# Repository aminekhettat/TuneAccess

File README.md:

# TuneAccess
Music instrument tuner adapted for people with visual disability

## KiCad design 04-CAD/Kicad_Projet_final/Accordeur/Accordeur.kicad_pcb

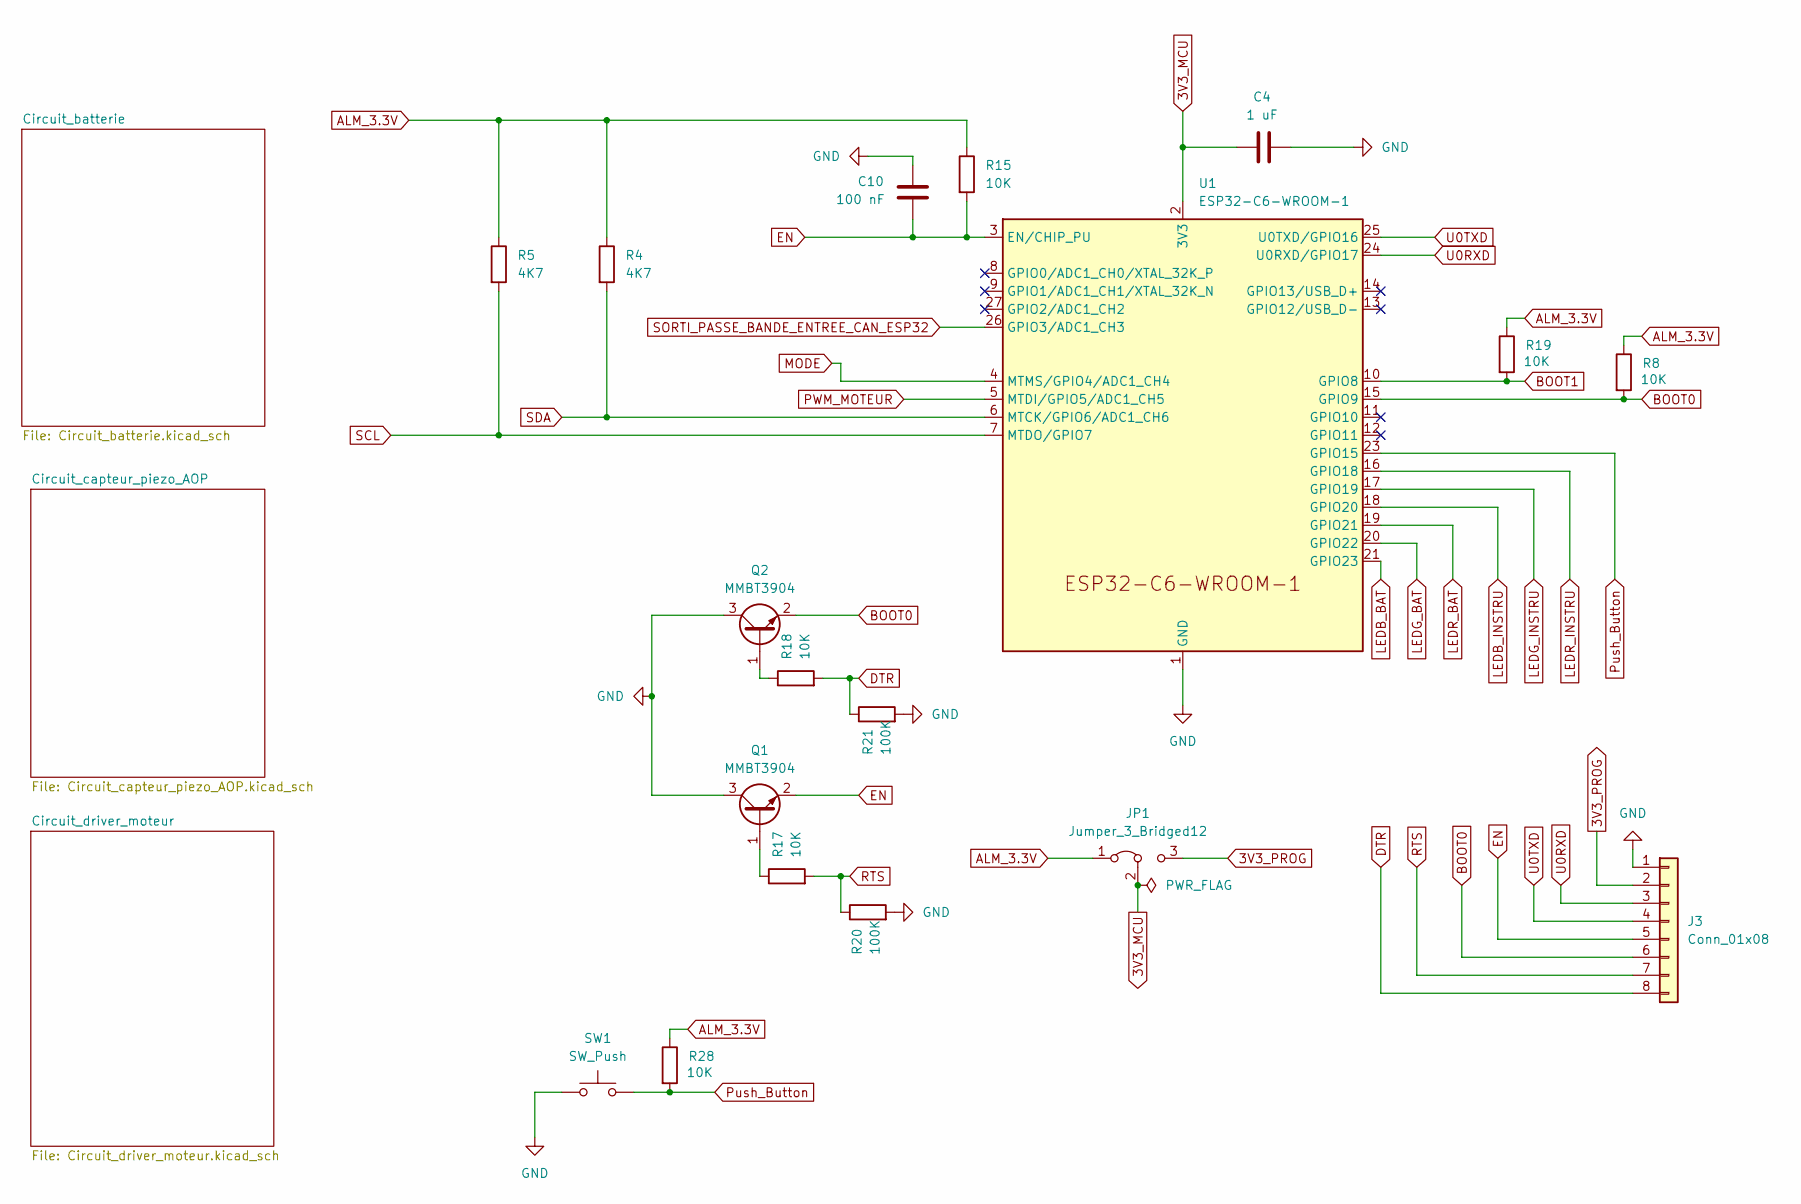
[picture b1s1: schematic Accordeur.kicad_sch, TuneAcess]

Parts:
C4: 1 uF; C_0805_2012Metric
C10: 100 nF; C_0805_2012Metric
J3: Conn_01x08; PinHeader_1x08_P2.54mm_Horizontal
JP1: Jumper_3_Bridged12; PinHeader_1x03_P2.54mm_Vertical
Q1, Q2: MMBT3904; SOT-23
R4, R5: 4K7; R_0402_1005Metric
R8, R15, R17, R18, R19, R28: 10K; R_0402_1005Metric
R20, R21: 100K; R_0402_1005Metric
SW1: SW_Push; SW_PUSH_6mm_H13mm
U1: ESP32-C6-WROOM-1

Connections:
3V3_MCU: C4.2, JP1.2 (C), U1.2 (3V3)
3V3_PROG: J3.2, JP1.3 (B)
ALM_3.3V: JP1.1 (A), R4.1, R5.1, R8.1, R15.1, R19.1, R28.1; also elsewhere on the board
BOOT0: J3.6, Q2.2 (E), R8.2, U1.15 (GPIO9)
BOOT1: R19.2, U1.10 (GPIO8)
DTR: J3.8, R18.2, R21.1
EN: C10.2, J3.5, Q1.2 (E), R15.2, U1.3 (EN/CHIP_PU)
GND: C4.1, C10.1, J3.1, Q1.3 (C), Q2.3 (C), R20.2, R21.2, SW1.1, U1.1 (GND), U1.28 (GND), U1.29 (GND); also elsewhere on the board
LEDB_BAT: U1.21 (GPIO23); also elsewhere on the board
LEDB_INSTRU: U1.18 (GPIO20); also elsewhere on the board
LEDG_BAT: U1.20 (GPIO22); also elsewhere on the board
LEDG_INSTRU: U1.17 (GPIO19); also elsewhere on the board
LEDR_BAT: U1.19 (GPIO21); also elsewhere on the board
LEDR_INSTRU: U1.16 (GPIO18); also elsewhere on the board
MODE: U1.4 (MTMS/GPIO4/ADC1_CH4); also elsewhere on the board
unnamed: Q1.1 (B), R17.1
unnamed: Q2.1 (B), R18.1
PWM_MOTEUR: U1.5 (MTDI/GPIO5/ADC1_CH5); also elsewhere on the board
Push_Button: R28.2, SW1.2, U1.23 (GPIO15)
RTS: J3.7, R17.2, R20.1
SCL: R5.2, U1.7 (MTDO/GPIO7); also elsewhere on the board
SDA: R4.2, U1.6 (MTCK/GPIO6/ADC1_CH6); also elsewhere on the board
SORTI_PASSE_BANDE_ENTREE_CAN_ESP32: U1.26 (GPIO3/ADC1_CH3); also elsewhere on the board
U0RXD: J3.3, U1.24 (U0RXD/GPIO17)
U0TXD: J3.4, U1.25 (U0TXD/GPIO16)

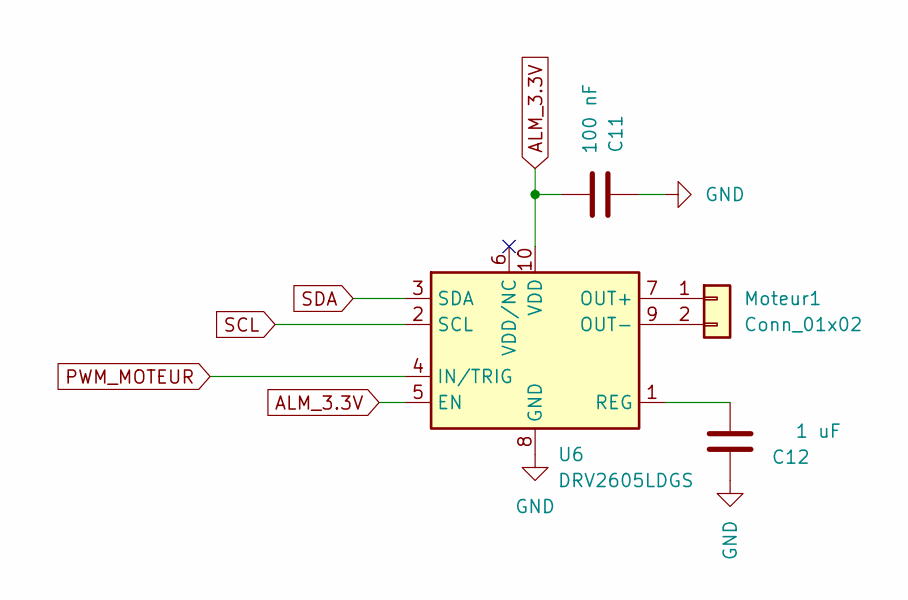
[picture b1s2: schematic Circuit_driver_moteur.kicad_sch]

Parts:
C11: 100 nF; C_0805_2012Metric
C12: 1 uF; C_0805_2012Metric
Moteur1: Conn_01x02; TerminalBlock_Phoenix_PT-1,5-2-3.5-H_1x02_P3.50mm_Horizontal
U6: DRV2605LDGS; SSOP-10_3.9x4.9mm_P1.00mm

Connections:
ALM_3.3V: C11.2, U6.5 (EN), U6.10 (VDD); also elsewhere on the board
GND: C11.1, C12.1, U6.8 (GND); also elsewhere on the board
unnamed: Moteur1.1, U6.7 (OUT+)
unnamed: Moteur1.2, U6.9 (OUT-)
unnamed: C12.2, U6.1 (REG)
PWM_MOTEUR: U6.4 (IN/TRIG); also elsewhere on the board
SCL: U6.2 (SCL); also elsewhere on the board
SDA: U6.3 (SDA); also elsewhere on the board

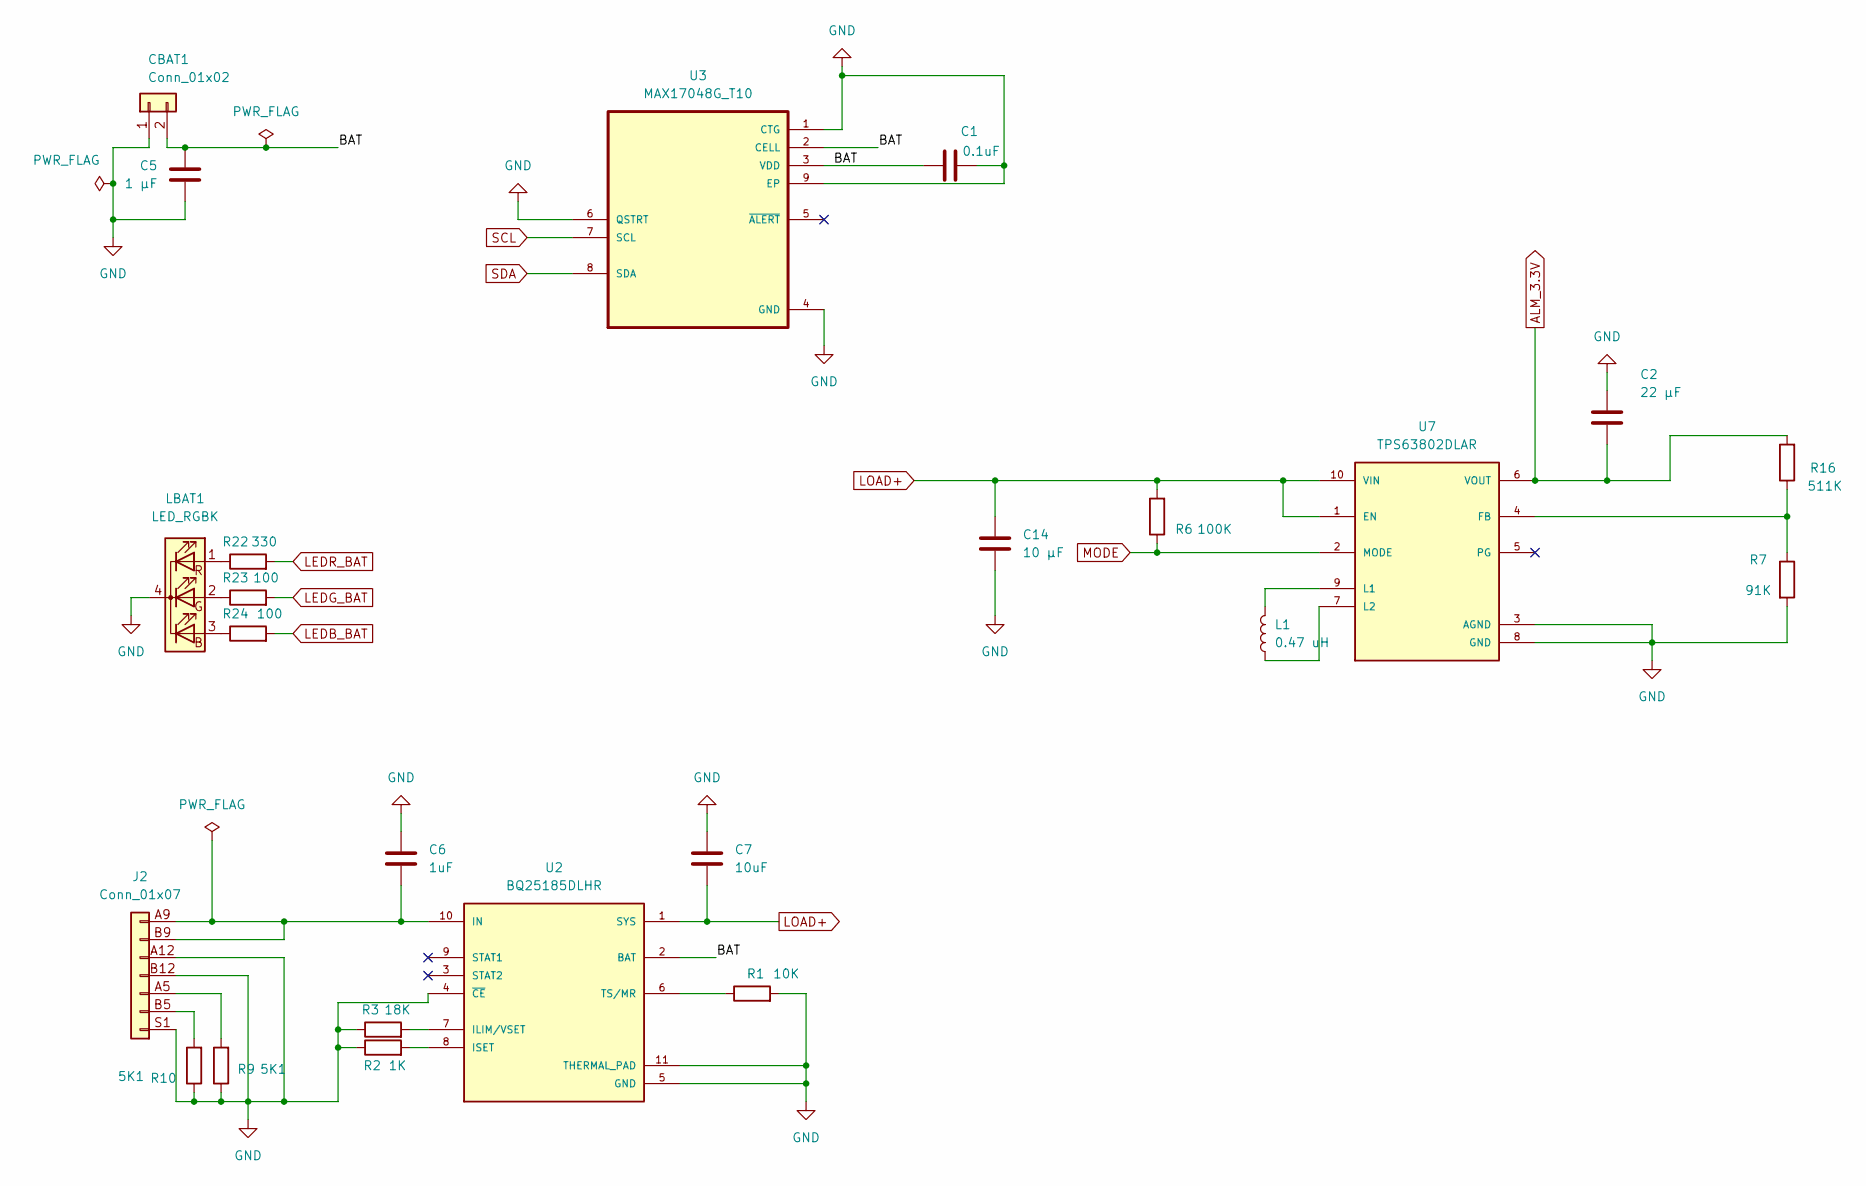
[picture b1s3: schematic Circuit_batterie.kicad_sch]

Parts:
C1: 0.1uF; C_0805_2012Metric
C2: 22 µF; C_1210_3225Metric
C5: 1 µF; C_0805_2012Metric
C6: 1uF; C_0805_2012Metric
C7: 10uF; C_0805_2012Metric
C14: 10 µF; C_0805_2012Metric
CBAT1: Conn_01x02; JST_PH_S2B-PH-K_1x02_P2.00mm_Horizontal
J2: Conn_01x07; USB_C_Receptacle_GCT_USB4125-xx-x-0190_6P_TopMnt_Horizontal
L1: 0.47 uH; L_Coilcraft_XAL4020-XXX
LBAT1: LED_RGBK; LED_D5.0mm-4_RGB
R1: 10K; R_0402_1005Metric
R2: 1K; R_0402_1005Metric
R3: 18K; R_0402_1005Metric
R6: 100K; R_0402_1005Metric
R7: 91K; R_0402_1005Metric
R9, R10: 5K1; R_0402_1005Metric
R16: 511K; R_0402_1005Metric
R22: 330; R_0402_1005Metric
R23, R24: 100; R_0402_1005Metric
U2: BQ25185DLHR; Texas_DLH0010A_WSON-10-1EP_2.2x2mm_P0.4mm_EP0.9x1.5mm_Therm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; PARTREV OCTOBER 2023
U3: MAX17048G_T10; SON50P200X200X80-9N; DigiKey_Part_Number MAX17048G+T10CT-ND
U7: TPS63802DLAR; VREG_TPS63802DLAR; PARTREV B

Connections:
/Circuit_batterie/BAT: C1.2, C5.1, CBAT1.2, U2.2 (BAT), U3.2 (CELL), U3.3 (VDD)
ALM_3.3V: C2.1, R16.2, U7.6 (VOUT); also elsewhere on the board
GND: C1.1, C2.2, C5.2, C6.1, C7.1, C14.2, CBAT1.1, J2.A12 (Pin_5), J2.B12 (Pin_4), J2.S1 (Pin_1), LBAT1.4 (K), R1.2, R2.1, R3.1, R7.2, R9.1, R10.1, U2.4 (~CE), U2.5 (GND), U2.11 (THERMAL_PAD), U3.1 (CTG), U3.4 (GND), U3.6 (QSTRT), U3.9 (EP), U7.3 (AGND), U7.8 (GND); also elsewhere on the board
LEDB_BAT: R24.2; also elsewhere on the board
LEDG_BAT: R23.2; also elsewhere on the board
LEDR_BAT: R22.2; also elsewhere on the board
LOAD+: C7.2, C14.1, R6.2, U2.1 (SYS), U7.1 (EN), U7.10 (VIN)
MODE: R6.1, U7.2 (MODE); also elsewhere on the board
unnamed: J2.B5 (Pin_2), R10.2
unnamed: J2.A5 (Pin_3), R9.2
unnamed: C6.2, J2.A9 (Pin_7), J2.B9 (Pin_6), U2.10 (IN)
unnamed: LBAT1.3 (BA), R24.1
unnamed: LBAT1.2 (GA), R23.1
unnamed: LBAT1.1 (RA), R22.1
unnamed: R3.2, U2.7 (ILIM/VSET)
unnamed: R2.2, U2.8 (ISET)
unnamed: R1.1, U2.6 (TS/MR)
unnamed: R7.1, R16.1, U7.4 (FB)
unnamed: L1.2, U7.9 (L1)
unnamed: L1.1, U7.7 (L2)
SCL: U3.7 (SCL); also elsewhere on the board
SDA: U3.8 (SDA); also elsewhere on the board

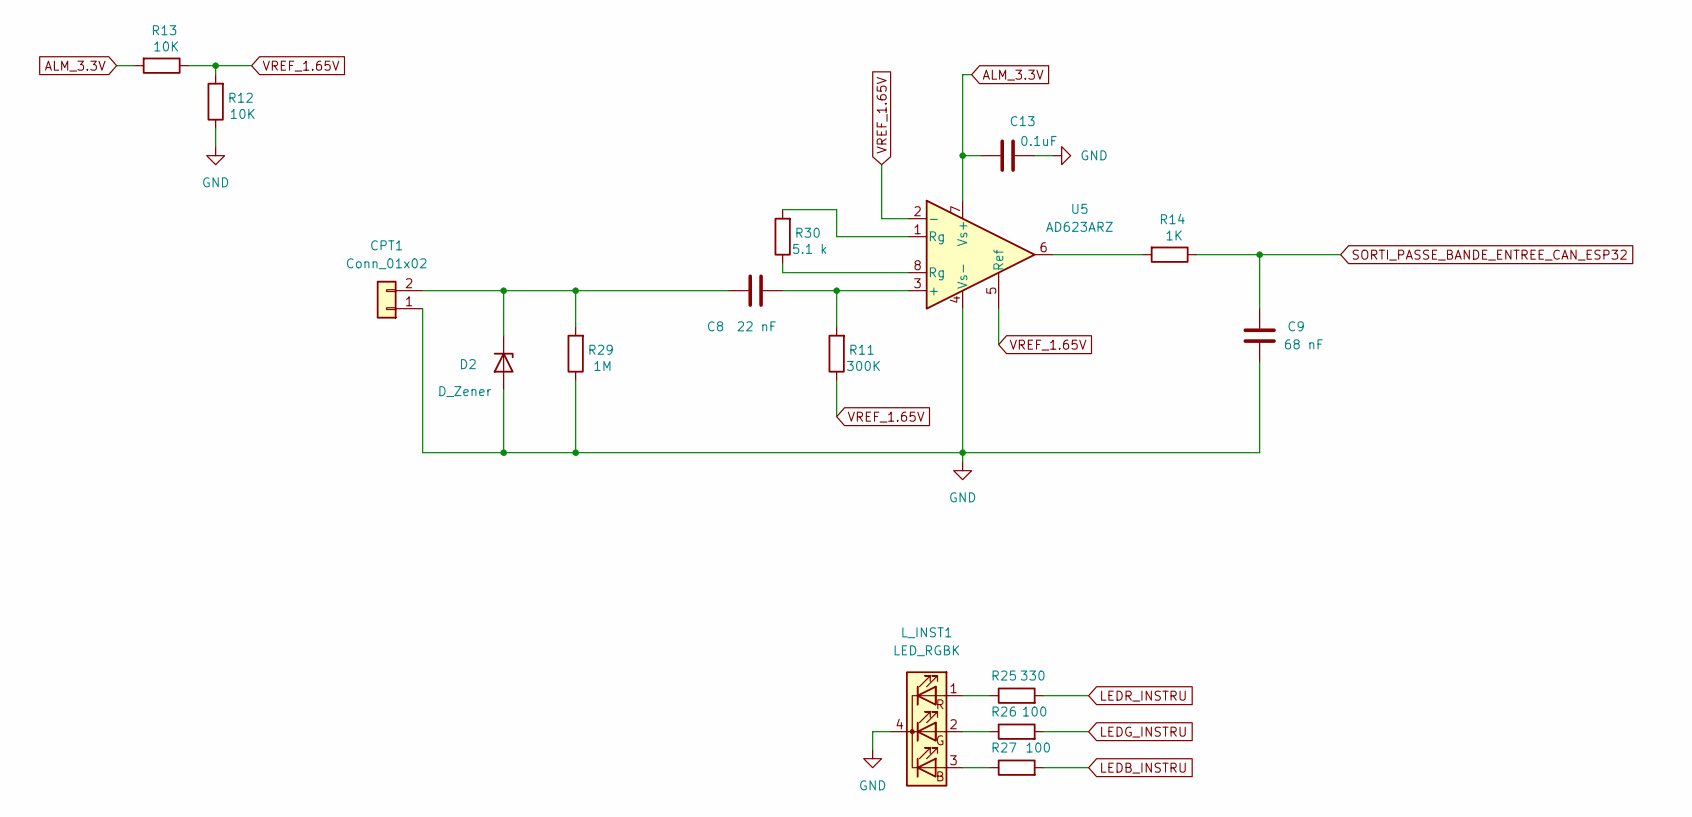
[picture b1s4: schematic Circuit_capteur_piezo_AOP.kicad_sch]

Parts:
C8: 22 nF; C_0805_2012Metric
C9: 68 nF; C_0805_2012Metric
C13: 0.1uF; C_0805_2012Metric
CPT1: Conn_01x02; TerminalBlock_Phoenix_PT-1,5-2-3.5-H_1x02_P3.50mm_Horizontal
D2: D_Zener; D_SOD-123
L_INST1: LED_RGBK; LED_D5.0mm-4_RGB
R11: 300K; R_0402_1005Metric
R12, R13: 10K; R_0402_1005Metric
R14: 1K; R_0402_1005Metric
R25: 330; R_0402_1005Metric
R26, R27: 100; R_0402_1005Metric
R29: 1M; R_0402_1005Metric
R30: 5.1 k; R_0402_1005Metric
U5: AD623ARZ; SOIC-8_3.9x4.9mm_P1.27mm

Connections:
ALM_3.3V: C13.2, R13.2, U5.7 (Vs+); also elsewhere on the board
GND: C9.2, C13.1, CPT1.1, D2.2 (A), L_INST1.4 (K), R12.1, R29.1, U5.4 (Vs-); also elsewhere on the board
LEDB_INSTRU: R27.2; also elsewhere on the board
LEDG_INSTRU: R26.2; also elsewhere on the board
LEDR_INSTRU: R25.2; also elsewhere on the board
unnamed: C8.2, CPT1.2, D2.1 (K), R29.2
unnamed: L_INST1.3 (BA), R27.1
unnamed: L_INST1.2 (GA), R26.1
unnamed: L_INST1.1 (RA), R25.1
unnamed: R14.2, U5.6
unnamed: R30.1, U5.8 (Rg)
unnamed: R30.2, U5.1 (Rg)
unnamed: C8.1, R11.2, U5.3 (+)
SORTI_PASSE_BANDE_ENTREE_CAN_ESP32: C9.1, R14.1; also elsewhere on the board
VREF_1.65V: R11.1, R12.2, R13.1, U5.2 (-), U5.5 (Ref)

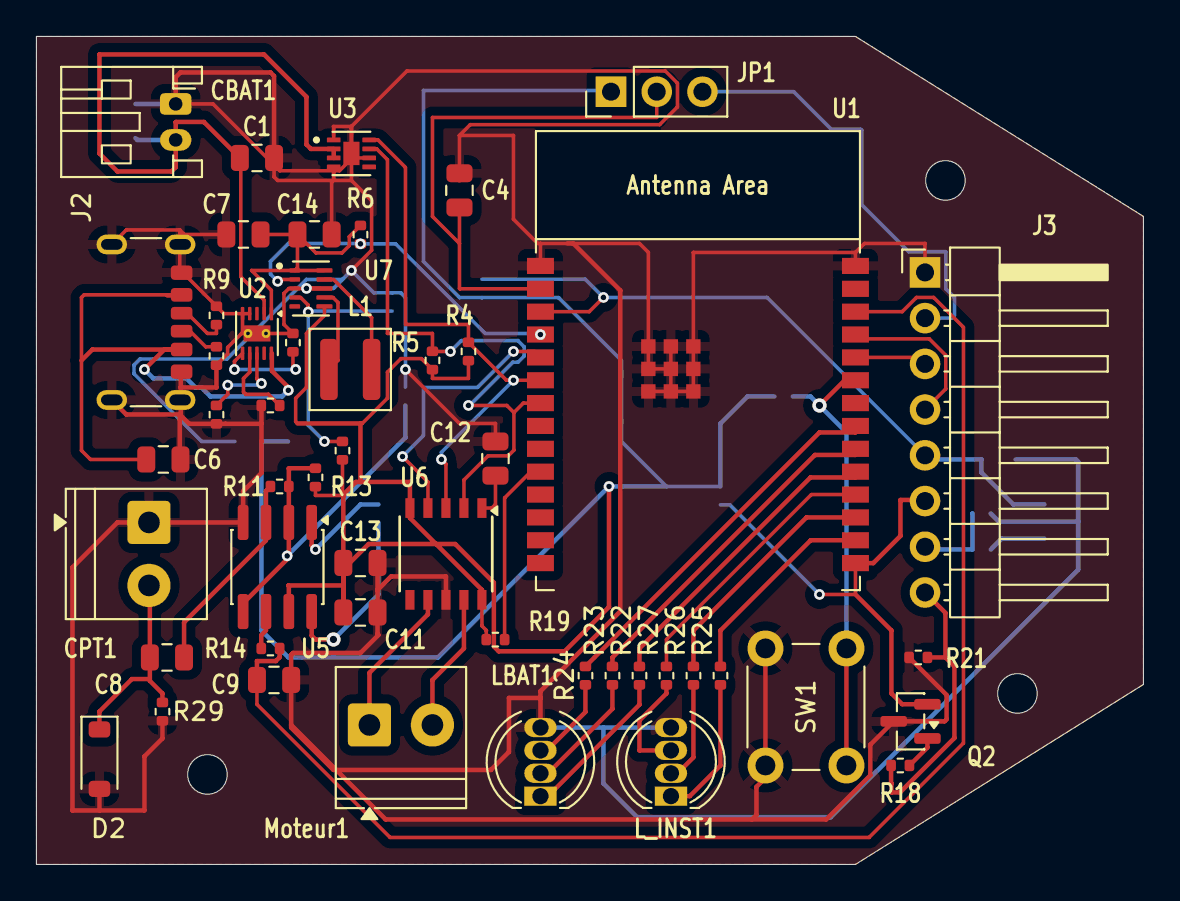
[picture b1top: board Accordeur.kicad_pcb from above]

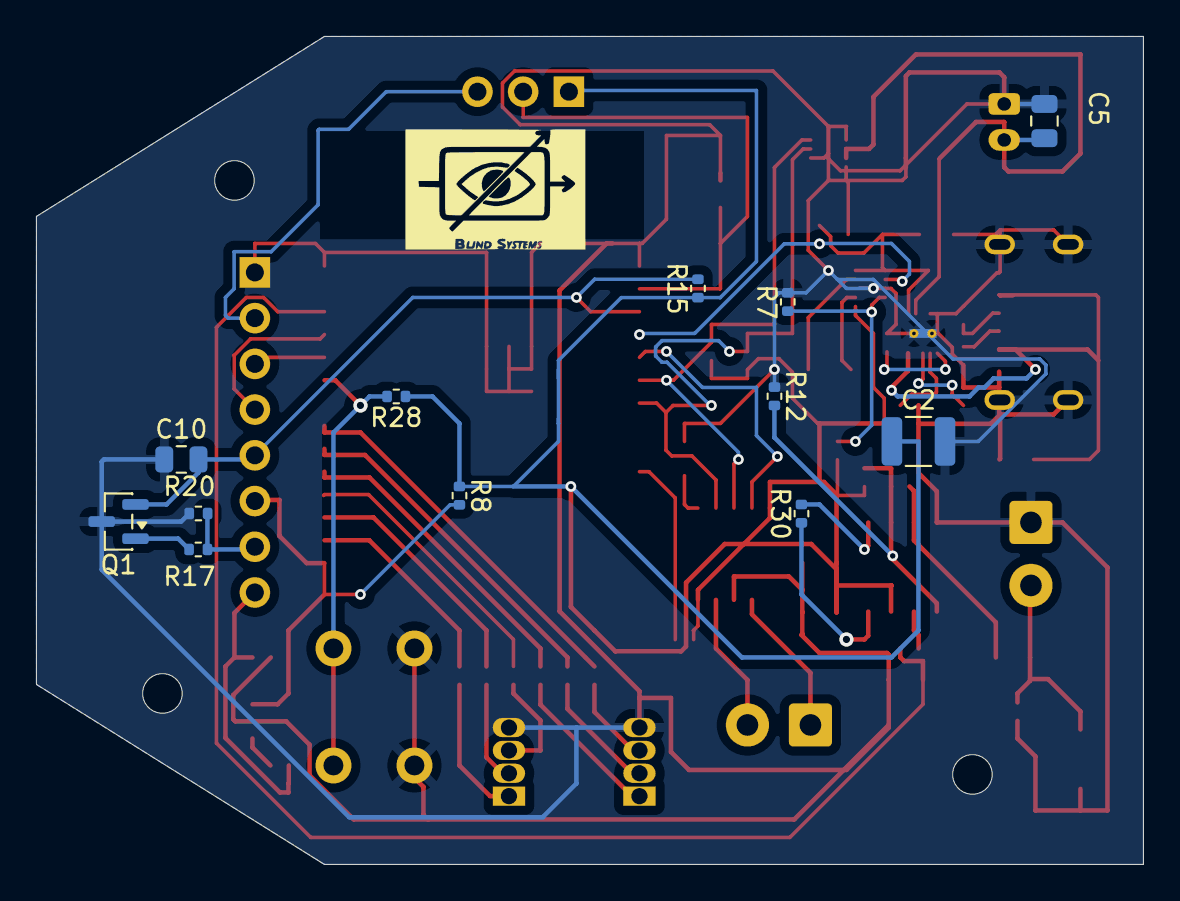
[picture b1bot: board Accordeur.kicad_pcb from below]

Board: 2 copper layers, 61.5 x 46.0 mm, 62 parts (12 on the bottom side), 51 nets.

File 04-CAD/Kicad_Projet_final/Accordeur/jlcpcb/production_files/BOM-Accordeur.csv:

Comment,Designator,Footprint,LCSC,Quantity
0.1uF,"C1,C13",C_0805_2012Metric,C126469,2
0.47 uH,L1,L_Coilcraft_XAL4020-XXX,C5837785,1
1 uF,"C12,C4",C_0805_2012Metric,C1712,2
1 µF,C5,C_0805_2012Metric,C1712,1
10 µF,C14,C_0805_2012Metric,C1713,1
100,"R23,R24,R26,R27",R_0402_1005Metric,C25076,4
100 nF,"C10,C11",C_0805_2012Metric,C1711,2
100K,"R20,R21,R6",R_0402_1005Metric,C25741,3
10K,"R1,R12,R13,R15,R17,R18,R19,R28,R8",R_0402_1005Metric,C25744,9
10uF,C7,C_0805_2012Metric,C1713,1
18K,R3,R_0402_1005Metric,C25762,1
1K,"R14,R2",R_0402_1005Metric,C11702,2
1M,R29,R_0402_1005Metric,C26083,1
1uF,C6,C_0805_2012Metric,C1712,1
22 nF,C8,C_0805_2012Metric,C51574,1
22 µF,C2,C_1210_3225Metric,C21397,1
300K,R11,R_0402_1005Metric,C138011,1
330,"R22,R25",R_0402_1005Metric,C25104,2
4K7,"R4,R5",R_0402_1005Metric,C174364,2
5.1 k,R30,R_0402_1005Metric,C25905,1
511K,R16,R_0402_1005Metric,C64042,1
5K1,"R10,R9",R_0402_1005Metric,C105872,2
68 nF,C9,C_0805_2012Metric,C1756,1
91K,R7,R_0402_1005Metric,C4147,1
AD623ARZ,U5,SOIC-8_3.9x4.9mm_P1.27mm,C9676,1
BQ25185DLHR,U2,Texas_DLH0010A_WSON-10-1EP_2.2x2mm_P0.4mm_EP0.9x1.5mm_ThermalVias,C19725033,1
Conn_01x02,CBAT1,JST_PH_S2B-PH-K_1x02_P2.00mm_Horizontal,C265016,1
Conn_01x02,"CPT1,Moteur1","TerminalBlock_Phoenix_PT-1,5-2-3.5-H_1x02_P3.50mm_Horizontal",C474896,2
Conn_01x07,J2,USB_C_Receptacle_GCT_USB4125-xx-x-0190_6P_TopMnt_Horizontal,C283540,1
Conn_01x08,J3,PinHeader_1x08_P2.54mm_Horizontal,C492416,1
DRV2605LDGS,U6,SSOP-10_3.9x4.9mm_P1.00mm,C527464,1
D_Zener,D2,D_SOD-123,C2112,1
ESP32-C6-WROOM-1,U1,ESP32-C6-WROOM-1,C5366877,1
Jumper_3_Bridged12,JP1,PinHeader_1x03_P2.54mm_Vertical,C49257,1
LED_RGBK,"LBAT1,L_INST1",LED_D5.0mm-4_RGB,C20613340,2
MAX17048G_T10,U3,SON50P200X200X80-9N,C2682616,1
MMBT3904,"Q1,Q2",SOT-23,C20526,2
SW_Push,SW1,SW_PUSH_6mm_H13mm,C22397147,1
TPS63802DLAR,U7,VREG_TPS63802DLAR,C2845237,1

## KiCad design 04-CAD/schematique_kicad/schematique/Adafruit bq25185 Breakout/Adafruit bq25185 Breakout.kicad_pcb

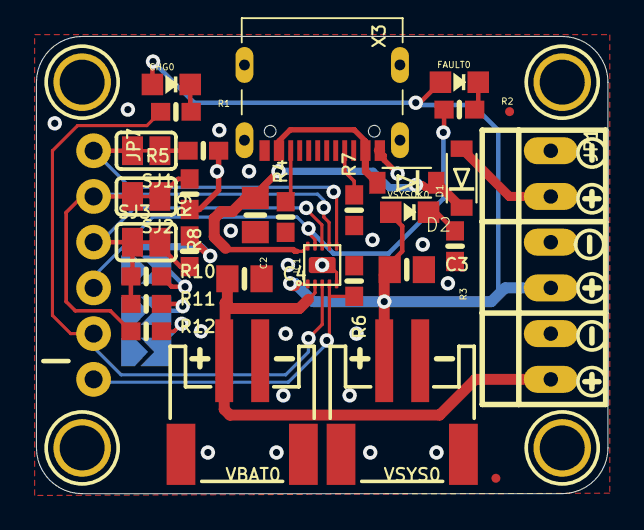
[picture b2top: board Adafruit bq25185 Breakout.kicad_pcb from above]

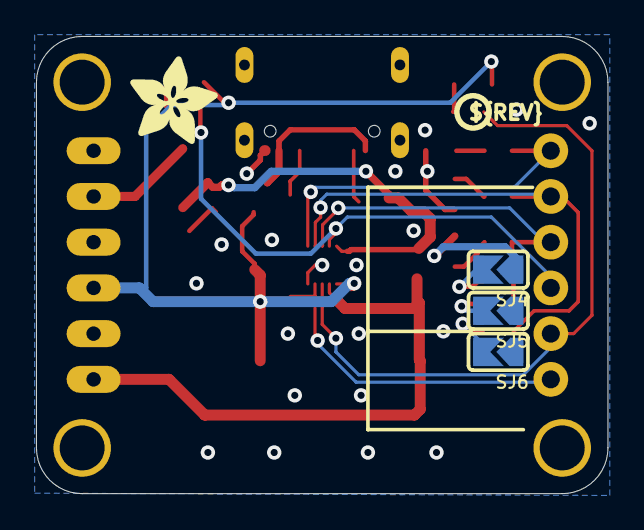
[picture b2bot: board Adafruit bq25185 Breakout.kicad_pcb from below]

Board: 2 copper layers, 31.8 x 25.4 mm, 69 parts (13 on the bottom side), 23 nets.

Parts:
C2, C3, C4: 22uF; 0805-NO
CHG0: ORANGE; CHIPLED_0805_NOOUTLINE
D1, D2: MBRX120; SOD-123FL
FAULT0: RED; CHIPLED_0805_NOOUTLINE
IC1: BQ25185; WSON10
JP1: 1X06_OVALWAVE
JP2, JP4: FIDUCIAL1.5X3; FIDUCIAL_0.5MM
JP7: 1X06_ROUND_76
PLABEL0: PLABEL0
PLABEL1: PLABEL1
PLABEL2: PLABEL2
PLABEL3: PLABEL3
PLABEL4: PLABEL4
PLABEL5: PLABEL5
PLABEL6: PLABEL6
PLABEL7: PLABEL7
PLABEL8: PLABEL8
PLABEL9: PLABEL9
PLABEL10: PLABEL10
PLABEL11: PLABEL11
PLABEL12: PLABEL12
PLABEL13: PLABEL13
PLABEL14: PLABEL14
PLABEL15: PLABEL15
PLABEL16: PLABEL16
PLABEL17: PLABEL17
PLABEL18: PLABEL18
PLABEL19: PLABEL19
PLABEL20: PLABEL20
PLABEL21: PLABEL21
PLABEL22: PLABEL22
R1, R2, R3: 1K; 0603-NO
R4, R7, R12: 5.1K; 0603-NO
R5, R6: 10K; 0603-NO
R8: 13K; 0603-NO
R9: 600; 0603-NO
R10: 300; 0603-NO
R11: 1200; 0603-NO
SJ1, SJ2, SJ3: SOLDERJUMPER_CLOSEDWIRE
SJ4, SJ5, SJ6: SOLDERJUMPER_ARROW_NOPASTE
U$11, U$16, U$18, U$19: MOUNTINGHOLE2.5; MOUNTINGHOLE_2.5_PLATED
U$23, U$27, U$28: SYMBOL_PLUS
U$24, U$25, U$26: SYMBOL_MINUS
U$46: ADAFRUIT_5MM
U$47: PCBFEAT-REV-040
VBAT0: JST2PH; JSTPH2_BATT
VSYS0: JST2PH; JSTPH2_BATT
VSYSOK0: GREEN; CHIPLED_0805_NOOUTLINE
X3: USBC; USB_C_CUSB31-CFM2AX-01-X

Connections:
5.0V: C3.1, CHG0.A, FAULT0.A, IC1.1, JP1.4, VSYS0.2, VSYSOK0.A
/CE: IC1.4, JP7.6, R6.2
GND: C2.2, C3.2, C4.2, IC1.5, IC1.PAD, JP1.1, JP1.3, JP1.5, R3.2, R4.1, R5.1, R6.1, R7.1, R8.2, R9.2, SJ4.1, SJ5.1, SJ6.1, VBAT0.1, VBAT0.NC1, VBAT0.NC2, VSYS0.1, VSYS0.NC1, VSYS0.NC2, X3.A1B12, X3.B1A12
ISET: IC1.8, JP7.3, R10.1, R11.1, SJ3.1
unnamed: CHG0.C, R1.2
unnamed: FAULT0.C, R2.2
unnamed: R8.1, SJ2.1
unnamed: R4.2, X3.B5
unnamed: R5.2, SJ1.1
unnamed: R7.2, X3.A5
unnamed: R9.1, SJ3.2
unnamed: R10.2, SJ4.2
unnamed: R11.2, SJ5.2
unnamed: R12.2, SJ6.2
unnamed: D1.A, JP1.2
unnamed: R3.1, VSYSOK0.C
STAT1: IC1.9, JP7.4, R2.1
STAT2: IC1.3, JP7.5, R1.1
THERM: IC1.6, JP7.1, SJ1.2
USB: D2.A, X3.A4B9, X3.B4A9
VBAT: C4.1, IC1.2, JP1.6, VBAT0.2
VBUS: C2.1, D1.C, D2.C, IC1.10
VSET: IC1.7, JP7.2, R12.1, SJ2.2

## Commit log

2025-10-31 Update file structure
2025-10-31 adding demo codes for speaker and microphone
2025-10-31 Code fonctionnel d'enregistrement au micro et d'écoute sur Haut parleur
2025-10-31 update_micro et doc_schema_bloc
2025-11-07 Implémentation de l'algorithme de YIN et génération de son
2026-02-24 TuneAcess2
2026-02-24 TuneAcess3
